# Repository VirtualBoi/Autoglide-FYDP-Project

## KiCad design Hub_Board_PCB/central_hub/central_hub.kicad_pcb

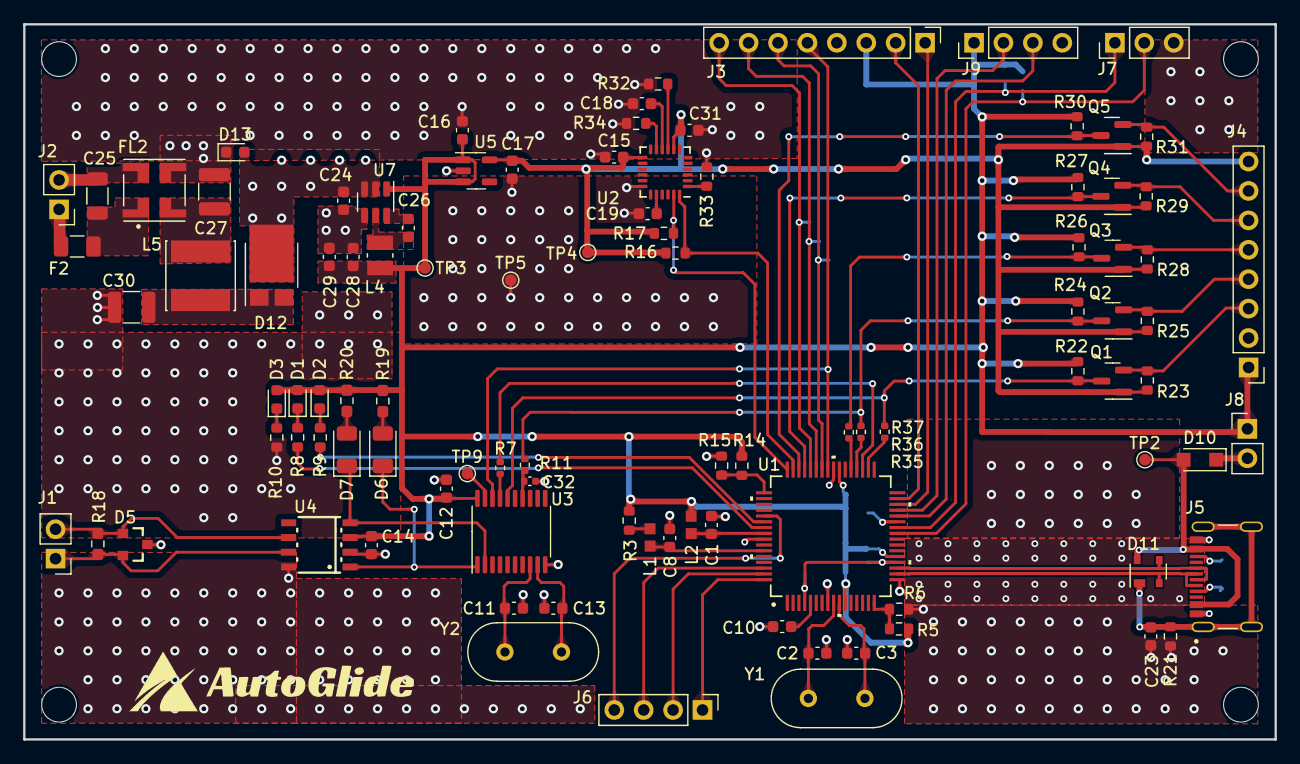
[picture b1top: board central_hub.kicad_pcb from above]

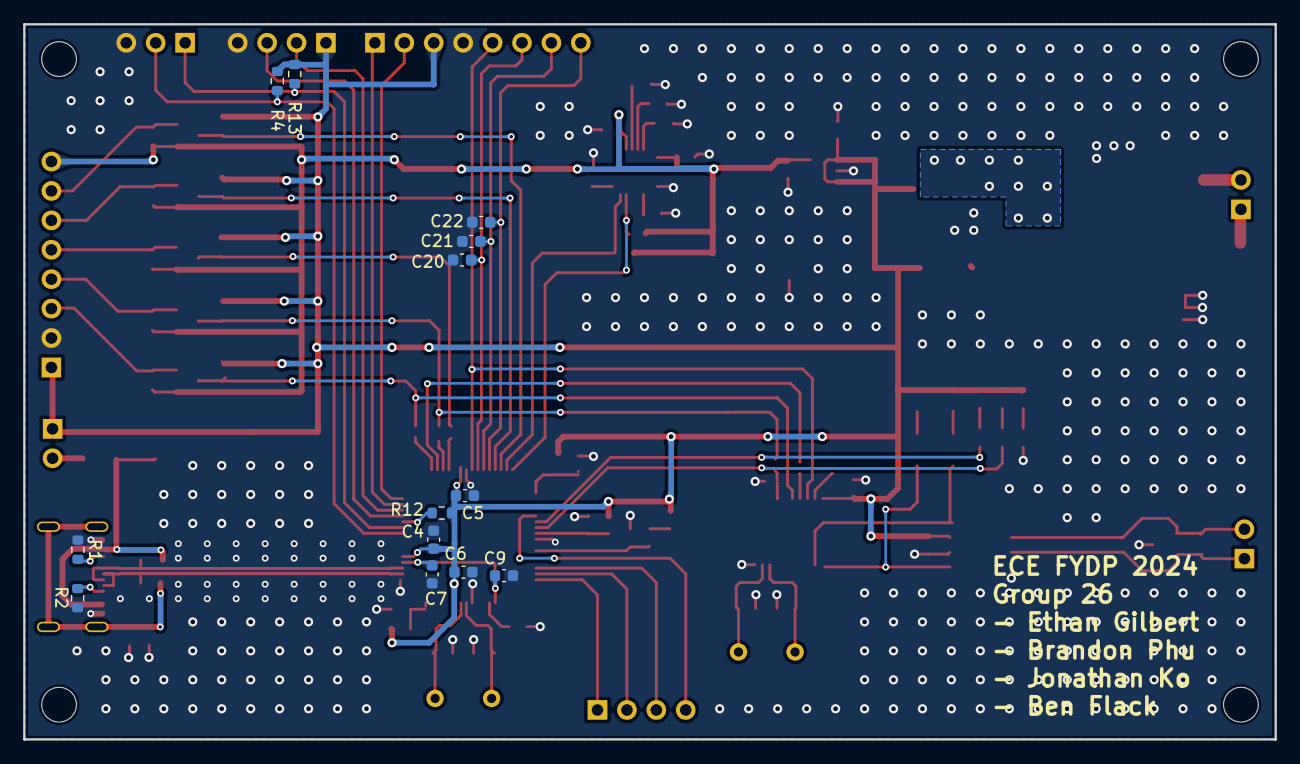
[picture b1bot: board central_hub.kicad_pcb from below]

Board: 2 copper layers, 108.0 x 61.7 mm, 116 parts (13 on the bottom side), 79 nets.

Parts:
C1, C5, C6, C9: 100nF; C_0603_1608Metric
C2, C3, C11, C13: 22p; C_0603_1608Metric
C4, C7, C10: 4.7uF; C_0603_1608Metric
C8: 1uF; C_0603_1608Metric
C12, C14, C15: 0.1u; C_0603_1608Metric
C16, C17: 1u; C_0603_1608Metric
C18: 0.1uF; C_0603_1608Metric
C19: 2.2n; C_0603_1608Metric
C20, C21, C22: 10nF; C_0603_1608Metric
C23: 4.7nF; C_0603_1608Metric
C24: 10u; C_0603_1608Metric
C25: 1u; C_1206_3216Metric
C26: 100n; C_0603_1608Metric
C27, C30: 10u; C_1210_3225Metric
C28, C29: 22u; C_0603_1608Metric
C31: 10n; C_0603_1608Metric
C32: 0.1u; C_0402_1005Metric
D1, D2, D3: LED; D_0603_1608Metric
D5: PESD1CAN; SOT23-3
D6, D7: LED; LED_1206_3216Metric
D10: PMEG6020AELRX; Nexperia_CFP3_SOD-123W
D11: PRTR5V0U2X,215; SOT-143
D12: PMEG030V050EPD; Nexperia_CFP15_SOT-1289
D13: 5.0SMDJ16CA; D_0603_1608Metric
F2: 0685T3000-01; Fuse_1206_3216Metric
FL2: DLW5BTM251TQ2L; FIL_DLW5BTZ251TQ2L
H1, H2, H3, H4: MountingHole; MountingHole_3mm
J1: CAN_OUT; PinHeader_1x02_P2.54mm_Vertical
J2, J8: Conn_01x02; PinHeader_1x02_P2.54mm_Vertical
J3, J4: Screw_Terminal_01x08; PinHeader_1x08_P2.54mm_Vertical
J5: CSP-USC16-TR; VALCON_CSP-USC16-TR
J6, J9: Screw_Terminal_01x04; PinHeader_1x04_P2.54mm_Vertical
J7: Conn_01x03; PinHeader_1x03_P2.54mm_Vertical
L1, L2: BLM18PG471SN1D; IND_BLM18_0603_MUR
L4: DFE252012F-4R7M=P2; INDC2520X120N
L5: VLS6045EX-100M; IND_VLS6045EX-100M
Q1, Q2, Q3, Q4, Q5: BSS138; SOT-23
R1, R2, R3, R4, R5, R12, R13: 5.1k; R_0603_1608Metric
R6, R22, R23, R24, R25, R26, R27, R28, R29, R30, R31: 10k; R_0603_1608Metric
R7, R11, R35, R36, R37: 0; R_0402_1005Metric
R8, R9, R10: 330; R_0603_1608Metric
R14: 100k; R_0603_1608Metric
R15: 13.7k; R_0603_1608Metric
R16, R17, R32, R33, R34: 4.7k; R_0603_1608Metric
R18: 120; R_0603_1608Metric_Pad0.98x0.95mm_HandSolder
R19, R20: 270; R_0603_1608Metric_Pad0.98x0.95mm_HandSolder
R21: 1M; R_0603_1608Metric
TP2, TP3, TP4, TP5, TP9: TestPoint; TestPoint_Pad_D1.0mm
U1: R7FA4M1AB3CFM; PLQP0064KB-C_REN
U2: MPU-6050; InvenSense_QFN-24_4x4mm_P0.5mm
U3: MCP2515-xST; TSSOP-20_4.4x6.5mm_P0.65mm
U4: TJA1050; SOT96-1
U5: AP2112K-3.3TRG1; SOT-23-5
U7: AP63205WU-7; TSOT-23-6
Y1, Y2: 8M; Crystal_HC49-U_Vertical

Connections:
+3.3V: C15.2, C17.2, C31.1, J4.8, Q1.1 (G), Q2.1 (G), Q3.1 (G), Q4.1 (G), Q5.1 (G), R16.1, R17.1, R23.1, R25.1, R28.1, R29.1, R31.1, TP4.1, U2.8 (VLOGIC), U2.13 (VDD), U5.5 (VOUT)
+5V: C4.2, C5.2, C6.2, C12.1, C14.1, C16.2, C28.2, C29.2, D1.2 (A), D2.2 (A), D3.2 (A), J3.3, J4.1, J8.1, J9.1, L2.2, L4.2, R3.1, R4.1, R5.1, R12.1, R13.1, R14.1, R19.1, R20.1, R22.1, R24.1, R26.1, R27.1, R30.1, TP3.1, U1.11 (VCC), U1.21 (VCC_USB_LDO), U1.39 (VCC), U3.20 (VDD), U4.3 (VCC), U5.1 (VIN), U5.3 (EN), U7.1 (FB)
+12V: C24.2, D12.3 (K), D13.2 (A2), U7.2 (EN), U7.3 (IN)
+BATT: F2.1, J2.1
-BATT: C25.1, FL2.4, J2.2
/CAN/CAN_HI: D5.2, J1.1, R18.2, U4.7 (CANH)
/CAN/CAN_LOW: D5.1, J1.2, R18.1, U4.6 (CANL)
/Connectors/SHIELD2: C23.2, D11.1 (GND), J5.S1 (SHELL_GND), J5.S2 (SHELL_GND), J5.S3 (SHELL_GND), J5.S4 (SHELL_GND), R21.1
/MCU/AREF: L1.2, R3.2
/MCU/MCU_3V3: C7.2, C9.2, U1.4 (VBATT), U1.20 (VCC_USB)
/MCU/P012: R8.2, U1.55 (VREFH/AN007/P012)
/MCU/P013: R9.2, U1.54 (VREFL/AN008/P013)
A0: J6.4, U1.53 (DA0/AN009/P014)
A1: J6.1, U1.64 (AN000/P000)
A2: J6.2, U1.63 (AN001/P001)
A3: J6.3, U1.62 (AN002/P002)
BOOT: J7.1, R13.2, U1.26 (MD/P201)
CC1: J5.A5 (CC1), R2.1
CC2: J5.B5 (CC2), R1.1
D0: J3.2, U1.31 (GTIOC4B/P301)
D1: J3.1, U1.30 (GTIOC4A/P302)
D2: C21.1, J3.7, U1.43 (GTIOC1A/P105)
D3: C22.1, J3.8, U1.44 (GTIOC1B/P104)
D4: Q4.3 (D), R27.2, U1.45 (GTIOC2A/AN019/P103)
D4_3.3V: J4.6, Q4.2 (S), R29.2
D5: Q5.3 (D), R30.2, U1.46 (ADTRG0/GTIOC2B/AN020/P102)
D5_3.3V: J4.7, Q5.2 (S), R31.2
D6: C20.1, J3.6, U1.42 (GTIOC0B/P106)
D7: J3.5, U1.41 (GTIOC0A/P107), U3.18 (~CS)
D8: J9.3, U1.28 (GTIOC7A/P304)
D9: J9.2, U1.29 (GTIOC7B/P303)
D10: Q3.3 (D), R26.2, R37.1
D10_3.3V: J4.5, Q3.2 (S), R28.2
D11: Q1.3 (D), R22.2, R35.1, U3.16 (SI)
D11_3.3V: J4.3, Q1.2 (S), R23.2
D12: R7.2, U1.35 (CRX0/TDI/GTIOC1B/P110)
D13: Q2.3 (D), R11.2, R24.2, R36.1
D13_3.3V: J4.4, Q2.2 (S), R25.2
GND: C1.1, C2.1, C3.1, C4.1, C5.1, C6.1, C7.1, C8.1, C9.1, C10.1, C11.1, C12.2, C13.1, C14.2, C15.1, C16.1, C17.1, C18.1, C19.1, C20.2, C21.2, C22.2, C23.1, C24.1, C27.1, C28.1, C29.1, C30.1, C31.2, C32.2, D5.3, D13.1 (A1), FL2.3, J3.4, J4.2, J5.A1 (GND_A), J5.A12 (GND_A), J5.B1 (GND_B), J5.B12 (GND_B), J7.3, J9.4, R1.2, R2.2, R6.2, R10.2, R15.2, R21.2, R32.2, R33.2, R34.2, TP5.1, U1.8 (VSS), U1.17 (VSS_USB), U1.40 (VSS), U1.57 (AVSS0), U2.18 (GND), U3.10 (VSS), U4.2 (GND), U4.8 (S), U5.2 (GND), U7.4 (GND)
unnamed: C25.2, F2.2, FL2.1
unnamed: C27.2, FL2.2, L5.1
unnamed: C30.2, D12.1 (A), D12.2 (A), L5.2
unnamed: D1.1 (K), R8.1
unnamed: D2.1 (K), R9.1
unnamed: D3.1 (K), R10.1
unnamed: D6.2 (A), R19.2
unnamed: D6.1 (K), U3.1 (TXCAN), U4.1 (TXD)
unnamed: D7.2 (A), R20.2
unnamed: D7.1 (K), U3.2 (RXCAN), U4.4 (RXD)
unnamed: C1.2, L2.1, U1.56 (AVCC0)
unnamed: R35.2, U1.34 (CTX0/TDO/SWO/GTIOC1A/P109)
unnamed: R14.2, R15.1, U1.49 (GTIOC2A/AN016/P500)
unnamed: R36.2, U1.36 (GTIOC3A/P111)
unnamed: R37.2, U1.37 (GTIOC3B/P112)
unnamed: R12.2, U1.27 (NMI/INPUT_ONLY_P200)
unnamed: C8.2, L1.1, U1.59 (P010/AN005/VREFH0)
unnamed: C3.2, U1.10 (P212/GTIOC0B/EXTAL), Y1.1
unnamed: C2.2, U1.9 (P213/GTIOC0A/XTAL), Y1.2
unnamed: R5.2, R6.1, U1.16 (P407/USB_VBUS/ADTRG0)
unnamed: C10.2, U1.5 (VCL)
unnamed: R32.1, U2.9 (AD0)
unnamed: R33.1, U2.1 (CLKIN)
unnamed: C19.2, U2.20 (CPOUT)
unnamed: R34.1, U2.11 (FSYNC)
unnamed: C18.2, U2.10 (REGOUT)
unnamed: C13.2, U3.9 (OSC1), Y2.1
unnamed: C11.2, U3.8 (OSC2), Y2.2
unnamed: C32.1, R11.1, U3.14 (SCK)
unnamed: R7.1, U3.17 (SO)
unnamed: TP9.1, U3.19 (~RESET)
unnamed: C26.1, U7.6 (BST)
unnamed: C26.2, L4.1, U7.5 (SW)
SCL_Accel: R17.2, U1.48 (GTIOC5B/AN022/P100), U2.23 (SCL)
SDA_Accel: R16.2, U1.47 (GTIOC5A/AN021/P101), U2.24 (SDA)
USB_D+: D11.3 (I/O2), J5.A6 (DP1), J5.B6 (DP2), U1.19 (P914/USB_DP)
USB_D-: D11.2 (I/O1), J5.A7 (DN1), J5.B7 (DN2), U1.18 (P915/USB_DM)
VUSB: D10.2 (A), D11.4 (VCC), J5.A4 (VBUS_A), J5.A9 (VBUS_A), J5.B4 (VBUS_B), J5.B9 (VBUS_B), TP2.1
VUSB_DIODE: D10.1 (K), J8.2
~RESET: J7.2, R4.2, U1.25 (~RES)

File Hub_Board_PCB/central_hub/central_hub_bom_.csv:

Component,Description,Part,References,Value,Footprint,Quantity Per PCB,Datasheet,fp,FP,Voltage,Colour,Check_prices,MF,MP,PROD_ID,Package,SnapEDA_Link,Availability,MANUFACTURER,MAXIMUM_PACKAGE_HEIGHT,PARTREV,Price,Purchase-URL,STANDARD,Tolerance
1,Unpolarized capacitor,C,C2 C3 C11 C13,22p,C_0603_1608Metric,4,~,0603,0603,,,,,,,,,,,,,,,,
2,Unpolarized capacitor,C,C19,2.2n,C_0603_1608Metric,1,~,,0603,,,,,,,,,,,,,,,,
3,Unpolarized capacitor,C,C23,4.7nF,C_0603_1608Metric,1,~,,0603,1kV,,,,,,,,,,,,,,,
4,Unpolarized capacitor,C,C31,10n,C_0603_1608Metric,1,~,,0603,,,,,,,,,,,,,,,,
5,Unpolarized capacitor,C,C1 C5 C6 C9 C12 C14 C15 C18 C26,100nF,C_0603_1608Metric,9,~,0603,0603,,,,,,,,,,,,,,,,
6,Unpolarized capacitor,C,C32,0.1u,C_0402_1005Metric,1,~,,0402,,,,,,,,,,,,,,,,
7,Unpolarized capacitor,C,C8 C16 C17,1uF,C_0603_1608Metric,3,~,,0603,,,,,,,,,,,,,,,,
8,Unpolarized capacitor,C,C25,1u,C_1206_3216Metric,1,~,,1206,,,,,,,,,,,,,,,,
9,Unpolarized capacitor,C,C4 C7 C10,4.7uF,C_0603_1608Metric,3,~,0603,0603,,,,,,,,,,,,,,,,
10,Unpolarized capacitor,C,C24,10u,C_0603_1608Metric,1,~,,0603,,,,,,,,,,,,,,,,
11,Unpolarized capacitor,C,C27 C30,10u,C_1210_3225Metric,2,~,,1210,,,,,,,,,,,,,,,,
12,Unpolarized capacitor,C,C28 C29,22u,C_0603_1608Metric,2,~,,0603,,,,,,,,,,,,,,,,
13,"400W bidirectional Transient Voltage Suppressor, 18.0Vr, SMA(DO-214AC)",SMAJ18CA,D13,5.0SMDJ16CA,D_0603_1608Metric,1,https://www.littelfuse.com/media?resourcetype=datasheets&ite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,,0603,,,,,,,,,,,,,,,,
14,Light emitting diode,LED,D1 D2 D3,LED,D_0603_1608Metric,3,~,,0603,,GREEN,,,,,,,,,,,,,,
15,Light emitting diode,LED,D6 D7,LED,LED_1206_3216Metric,2,~,,1206,,,,,,,,,,,,,,,,
16,50V Clamp 3A (8/20µs) Ipp Tvs Diode Surface Mount SOT-323,PESD1CAN,D5,PESD1CAN,SOT23-3,1,,,,,,https://www.snapeda.com/parts/PESD1CAN/Nexperia/view-part/?ref=eda,Nexperia USA,PESD1CAN,DIO-12501,SOT-23-3 NXP Semiconductors,https://www.snapeda.com/parts/PESD1CAN/Nexperia/view-part/?ref=snap,,,,,,,,
17,"30V, 5A low Vf MEGA Schottky barrier rectifier, SOT-1289",PMEG030V050EPD,D12,PMEG030V050EPD,Nexperia_CFP15_SOT-1289,1,https://assets.nexperia.com/documents/data-sheet/PMEG030V050EPD.pdf,,,,,,,,,,,,,,,,,,
18,"60V, 2A low leakage current MEGA Schottky barrier rectifier, SOD-123W",PMEG6020AELR,D10,PMEG6020AELRX,Nexperia_CFP3_SOD-123W,1,https://assets.nexperia.com/documents/data-sheet/PMEG6020AELR.pdf,,,,,,,,,,,,,,,,,,
19,"Ultra low capacitance double rail-to-rail ESD protection diode, SOT-143",PRTR5V0U2X,D11,"PRTR5V0U2X,215",SOT-143,1,https://assets.nexperia.com/documents/data-sheet/PRTR5V0U2X.pdf,,,,,,,,,,,,,,,,,,
20,Fuse,Fuse,F2,0685T3000-01,Fuse_1206_3216Metric,1,~,,1206,,,,,,,,,,,,,,,,
21,2 Line Common Mode Choke Surface Mount 250 Ohms @ 100 MHz 5A DCR 20mOhm,DLW5BTM251TQ2L,FL2,DLW5BTM251TQ2L,FIL_DLW5BTZ251TQ2L,1,,,,,,https://www.snapeda.com/parts/DLW5BTM251TQ2L/Murata/view-par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,Murata,DLW5BTM251TQ2L,,Horizontal-6 Murata,https://www.snapeda.com/parts/DLW5BTM251TQ2L/Murata/view-par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,In Stock,Murata Electronics,2.5 mm,N/A,None,https://www.snapeda.com/api/url_track_click_mouser/?unipart_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,Manufacturer recommendations,
22,"Generic screw terminal, single row, 01x02, script generated (kicad-library-utils/schlib/autogen/connector/)",Screw_Terminal_01x02,J1,CAN_OUT,PinHeader_1x02_P2.54mm_Vertical,1,~,,,,,,,,,,,,,,,,,,
23,CSP-USC16-TR Valcon USB Type C Surface Mount PCB Socket,CSP-USC16-TR,J5,CSP-USC16-TR,VALCON_CSP-USC16-TR,1,,,,,,https://www.snapeda.com/parts/CSP-USC16-TR/Valcon/view-part/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,Valcon,CSP-USC16-TR,,None,https://www.snapeda.com/parts/CSP-USC16-TR/Valcon/view-part/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,In Stock,Valcon,3.26 mm,A0,None,https://www.snapeda.com/api/url_track_click_mouser/?unipart_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,Manufacturer Recommendations,
24,"Generic connector, single row, 01x02, script generated (kicad-library-utils/schlib/autogen/connector/)",Conn_01x02,J2 J8,Conn_01x02,PinHeader_1x02_P2.54mm_Vertical,2,~,,,,,,,,,,,,,,,,,,
25,"Generic connector, single row, 01x03, script generated (kicad-library-utils/schlib/autogen/connector/)",Conn_01x03,J7,Conn_01x03,PinHeader_1x03_P2.54mm_Vertical,1,~,,,,,,,,,,,,,,,,,,
26,"Generic screw terminal, single row, 01x04, script generated (kicad-library-utils/schlib/autogen/connector/)",Screw_Terminal_01x04,J6 J9,Screw_Terminal_01x04,PinHeader_1x04_P2.54mm_Vertical,2,~,,,,,,,,,,,,,,,,,,
27,"Generic screw terminal, single row, 01x08, script generated (kicad-library-utils/schlib/autogen/connector/)",Screw_Terminal_01x08,J3 J4,Screw_Terminal_01x08,PinHeader_1x08_P2.54mm_Vertical,2,~,,,,,,,,,,,,,,,,,,
28,,BLM18PG471SN1D,L1 L2,BLM18PG471SN1D,IND_BLM18_0603_MUR,2,BLM18PG471SN1D,,0603,,,,,,,,,,,,,,,,
29,"Inductor with Inductance: 4.7uH Tol. +/-20%, Package: 1008 (2520)",DFE252012F-4R7M=P2,L4,DFE252012F-4R7M=P2,INDC2520X120N,1,,,,,,https://www.snapeda.com/parts/DFE252012F-4R7M=P2/Murata+Elec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,Murata Electronics,DFE252012F-4R7M=P2,,2520 Murata,https://www.snapeda.com/parts/DFE252012F-4R7M=P2/Murata+Elec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,In Stock,,,,None,https://www.snapeda.com/api/url_track_click_mouser/?unipart_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 Electronics&part_name=DFE252012F-4R7M=P2&search_term=dfe252012f-4r7m=p2,,
30,"10 µH Shielded Drum Core, Wirewound Inductor 3.4 A 47mOhm Nonstandard",VLS6045EX-100M,L5,VLS6045EX-100M,IND_VLS6045EX-100M,1,,,,,,https://www.snapeda.com/parts/VLS6045EX-100M/TDK/view-part/?ref=eda,TDK,VLS6045EX-100M,,NON STANDARD-2 TDK,https://www.snapeda.com/parts/VLS6045EX-100M/TDK/view-part/?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,In Stock,TDK,4.5 mm,N/A,None,https://www.snapeda.com/api/url_track_click_mouser/?unipart_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,Manufacturer Recommendations,
31,"50V Vds, 0.22A Id, N-Channel MOSFET, SOT-23",BSS138,Q1 Q2 Q3 Q4 Q5,BSS138,SOT-23,5,https://www.onsemi.com/pub/Collateral/BSS138-D.PDF,,,,,,,,,,,,,,,,,,
32,Resistor,R,R7 R11 R35 R36 R37,0,R_0402_1005Metric,5,~,,0402,,,,,,,,,,,,,,,,
33,Resistor,R,R18,120,R_0603_1608Metric_Pad0.98x0.95mm_HandSolder,1,~,,0603,,,,,,,,,,,,,,,,
34,Resistor,R,R19 R20,270,R_0603_1608Metric_Pad0.98x0.95mm_HandSolder,2,~,,0603,,,,,,,,,,,,,,,,
35,Resistor,R,R8 R9 R10,330,R_0603_1608Metric,3,~,,0603,,,,,,,,,,,,,,,,
36,Resistor,R,R16 R17 R32 R33 R34,4.7k,R_0603_1608Metric,5,~,,0603,,,,,,,,,,,,,,,,
37,Resistor,R,R1 R2 R3 R4 R5 R12 R13,5.1k,R_0603_1608Metric,7,~,0603,0603,,,,,,,,,,,,,,,,
38,Resistor,R,R6 R22 R23 R24 R25 R26 R27 R28 R29 R30 R31,10k,R_0603_1608Metric,11,~,,0603,,,,,,,,,,,,,,,,
39,Resistor,R,R15,13.7k,R_0603_1608Metric,1,~,,0603,,,,,,,,,,,,,,,,0.1%
40,Resistor,R,R14,100k,R_0603_1608Metric,1,~,,0603,,,,,,,,,,,,,,,,0.1%
41,Resistor,R,R21,1M,R_0603_1608Metric,1,~,,0603,,,,,,,,,,,,,,,,
42,"600mA low dropout linear regulator, with enable pin, 3.8V-6V input voltage range, 3.3V fixed positive output, SOT-23-5",AP2112K-3.3,U5,AP2112K-3.3TRG1,SOT-23-5,1,https://www.diodes.com/assets/Datasheets/AP2112.pdf,,,,,,,,,,,,,,,,,,
43,"2A, 1.1MHz Buck DC/DC Converter, fixed 5.0V output voltage, TSOT-23-6",AP63205WU,U7,AP63205WU-7,TSOT-23-6,1,https://www.diodes.com/assets/Datasheets/AP63200-AP63201-AP6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,,,,,,,,,,,,,,,,,,
44,"Stand-Alone CAN Controller with SPI Interface, TSSOP-20",MCP2515-xST,U3,MCP2515-xST,TSSOP-20_4.4x6.5mm_P0.65mm,1,http://ww1.microchip.com/downloads/en/DeviceDoc/21801e.pdf,,,,,,,,,,,,,,,,,,
45,"InvenSense 6-Axis Motion Sensor, Gyroscope, Accelerometer, I2C",MPU-6050,U2,MPU-6050,InvenSense_QFN-24_4x4mm_P0.5mm,1,https://invensense.tdk.com/wp-content/uploads/2015/02/MPU-60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,,,,,,,,,,,,,,,,,,
46,,R7FA4M1AB3CFM,U1,R7FA4M1AB3CFM,PLQP0064KB-C_REN,1,R7FA4M1AB3CFM,,,,,,,,,,,,,,,,,,
47,CAN 1MBd Silent 5V Automotive 8-Pin SO T/R,TJA1050,U4,TJA1050,SOT96-1,1,,,,,,https://www.snapeda.com/parts/TJA1050/NXP+Semiconductors/vie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,NXP Semiconductors,TJA1050,,None,https://www.snapeda.com/parts/TJA1050/NXP+Semiconductors/vie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,Not in stock,,,,None,,,
48,Two pin crystal,Crystal,Y1 Y2,8M,Crystal_HC49-U_Vertical,2,~,,,,,,,,,,,,,,,,,,





Component Groups:,49
Component Count:,107
Fitted Components:,104
Number of PCBs:,1
Total components:,104
Schematic Version:,
Schematic Date:,
PCB Variant:,default
BoM Date:,2023-12-22 5:23:04 PM
Schematic Source:,central_hub.kicad_sch
KiCad Version:,Eeschema 7.0.7

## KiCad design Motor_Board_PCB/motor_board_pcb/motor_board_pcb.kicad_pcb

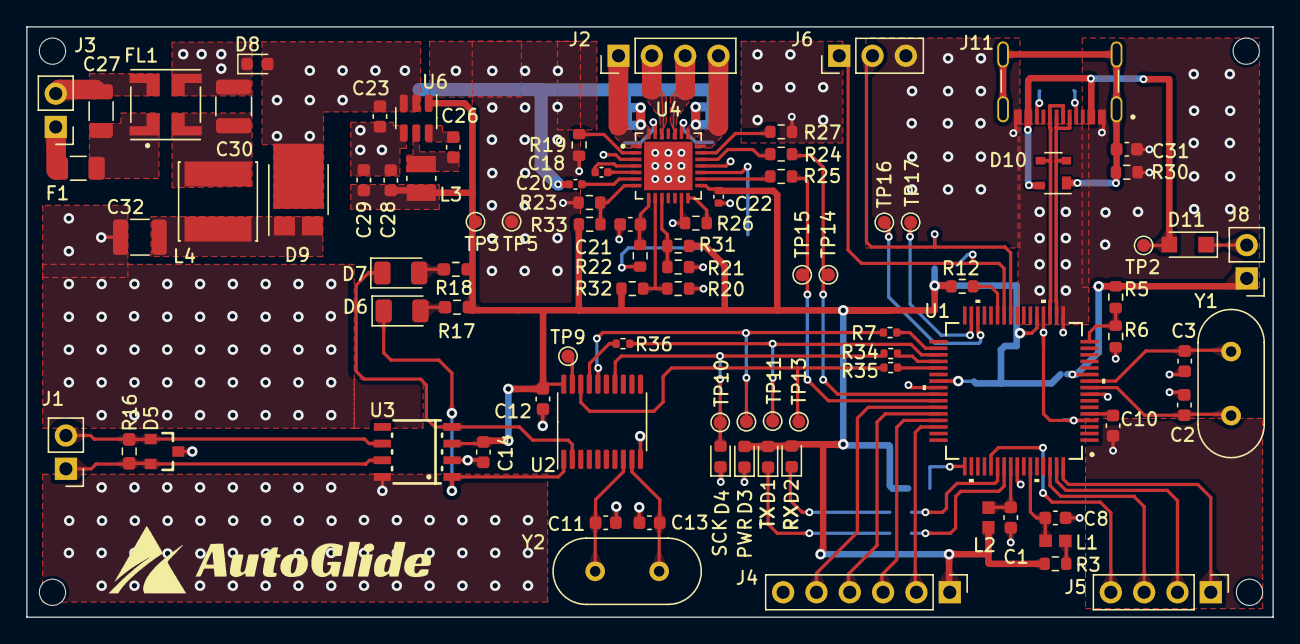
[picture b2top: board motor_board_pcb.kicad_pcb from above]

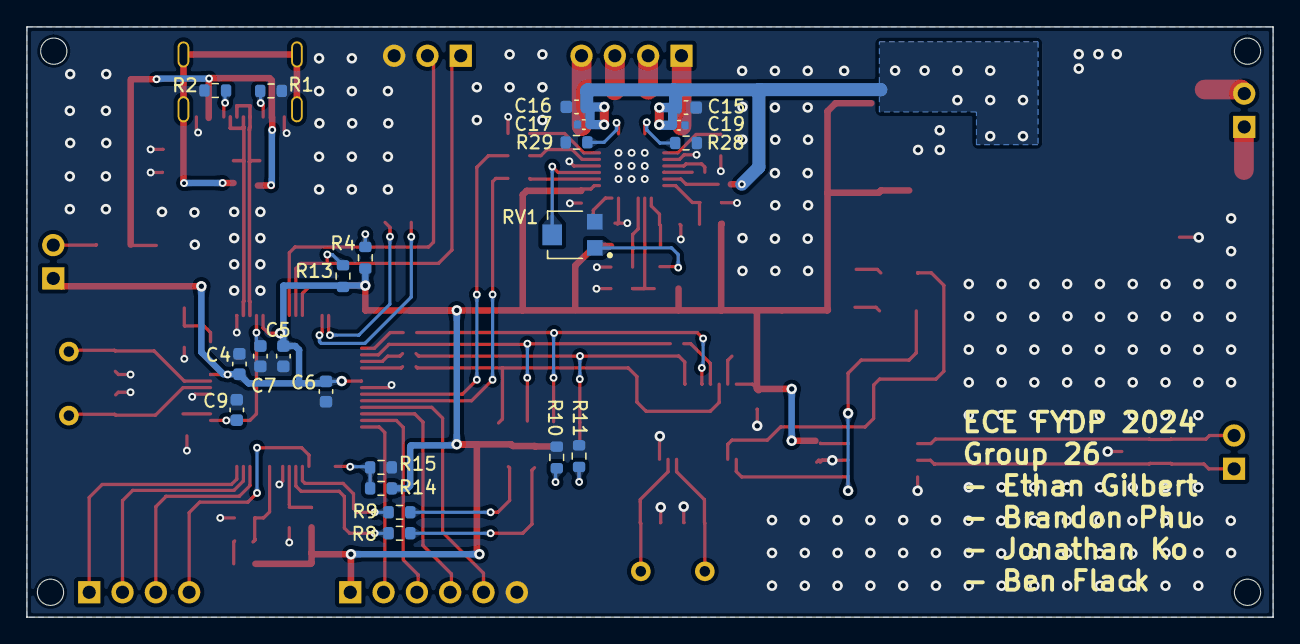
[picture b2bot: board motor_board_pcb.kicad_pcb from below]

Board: 2 copper layers, 95.0 x 45.0 mm, 111 parts (22 on the bottom side), 84 nets.

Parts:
C1, C5, C6, C9: 100nF; C_0603_1608Metric
C2, C3: 15pF; C_0603_1608Metric
C4, C7, C10: 4.7uF; C_0603_1608Metric
C8: 1uF; C_0603_1608Metric
C11, C13: 15p; C_0603_1608Metric
C12, C14: 0.1u; C_0603_1608Metric
C15, C16, C21: 4u7; C_0603_1608Metric
C17, C19, C20, C22: 100n; C_0402_1005Metric
C18: 22n; C_0402_1005Metric
C23: 10u; C_0603_1608Metric
C26: 100n; C_0603_1608Metric
C27: 1u; C_1206_3216Metric
C28, C29: 22u; C_0603_1608Metric
C30, C32: 10u; C_1210_3225Metric
C31: 4.7nF; C_0603_1608Metric
D1, D2, D3, D4: LED; D_0603_1608Metric
D5: PESD1CAN; SOT23-3
D6, D7: LED; LED_1206_3216Metric
D8: 5.0SMDJ16CA; D_0603_1608Metric
D9: PMEG030V050EPD; Nexperia_CFP15_SOT-1289
D10: PRTR5V0U2X,215; SOT-143
D11: PMEG6020AELRX; Nexperia_CFP3_SOD-123W
F1: 0685T3000-01; Fuse_1206_3216Metric
FL1: DLW5BTM251TQ2L; FIL_DLW5BTZ251TQ2L
J1: CAN_OUT; PinHeader_1x02_P2.54mm_Vertical
J2, J5: Screw_Terminal_01x04; PinHeader_1x04_P2.54mm_Vertical
J3, J8: Conn_01x02; PinHeader_1x02_P2.54mm_Vertical
J4: Screw_Terminal_01x06; PinHeader_1x06_P2.54mm_Vertical
J6: Conn_01x03; PinHeader_1x03_P2.54mm_Vertical
J11: CSP-USC16-TR; VALCON_CSP-USC16-TR
L1, L2: BLM18PG471SN1D; IND_BLM18_0603_MUR
L3: DFE252012F-4R7M=P2; INDC2520X120N
L4: VLS6045EX-100M; IND_VLS6045EX-100M
R1, R2, R3, R4, R5, R12, R13: 5.1k; R_0603_1608Metric
R6: 10k; R_0603_1608Metric
R7, R34, R35, R36: 0; R_0402_1005Metric
R8, R9, R10, R11: 330; R_0603_1608Metric
R14: 100k; R_0603_1608Metric
R15: 13.7k; R_0603_1608Metric
R16: 120; R_0603_1608Metric_Pad0.98x0.95mm_HandSolder
R17, R18: 270; R_0603_1608Metric_Pad0.98x0.95mm_HandSolder
R19, R20, R21, R22, R23, R26, R31, R32, R33: 10K; R_0603_1608Metric
R24, R25: 2k; R_0603_1608Metric
R27: 100K; R_0603_1608Metric
R28, R29: 0R11; R_0603_1608Metric
R30: 1M; R_0603_1608Metric
RV1: 10K; TRIM_TC33X-2-103E
TP2, TP3, TP5, TP9, TP10, TP11, TP12, TP13, TP14, TP15, TP16, TP17: TestPoint; TestPoint_Pad_D1.0mm
U1: R7FA4M1AB3CFM; PLQP0064KB-C_REN
U2: MCP2515-xST; TSSOP-20_4.4x6.5mm_P0.65mm
U3: TJA1050; SOT96-1
U4: TMC2209-LA; QFN50P500X500X90-29N
U6: AP63205WU-7; TSOT-23-6
Y1: 16MHz; Crystal_HC49-U_Vertical
Y2: 20M; Crystal_HC49-U_Vertical

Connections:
+5V: C4.2, C5.2, C6.2, C12.1, C14.1, C22.1, C28.2, C29.2, D1.2 (A), D2.2 (A), D3.2 (A), J4.1, J8.1, L2.2, L3.2, R3.1, R4.1, R5.1, R12.1, R13.1, R14.1, R17.1, R18.1, R31.2, R32.2, R33.2, TP3.1, U1.11 (VCC), U1.21 (VCC_USB_LDO), U1.39 (VCC), U2.20 (VDD), U3.3 (VCC), U4.15 (VCC_IO), U6.1 (FB)
+12V: C15.2, C16.2, C17.2, C19.2, C20.2, C23.2, D8.2 (A2), D9.3 (K), U4.22 (VS), U4.28 (VS), U6.2 (EN), U6.3 (IN)
+BATT: F1.1, J3.1
-BATT: C27.1, FL1.4, J3.2
/CAN/CAN_HI: D5.2, J1.1, R16.2, U3.7 (CANH)
/CAN/CAN_LOW: D5.1, J1.2, R16.1, U3.6 (CANL)
/Connectors/SHIELD2: C31.2, D10.1 (GND), J11.S1 (SHELL_GND), J11.S2 (SHELL_GND), J11.S3 (SHELL_GND), J11.S4 (SHELL_GND), R30.1
/MCU/AREF: L1.2, R3.2
/MCU/MCU_3V3: C7.2, C9.2, U1.4 (VBATT), U1.20 (VCC_USB)
/MCU/P012: R8.2, U1.55 (VREFH/AN007/P012)
/MCU/P013: R9.2, U1.54 (VREFL/AN008/P013)
/Motor_Driver/5VOUT: C21.2, R22.2, U4.8 (5VOUT)
/Motor_Driver/OUTA1: J2.3, U4.24 (OUTA1)
/Motor_Driver/OUTA2: J2.4, U4.21 (OUTA2)
/Motor_Driver/OUTB1: J2.2, U4.26 (OUTB1)
/Motor_Driver/OUTB2: J2.1, U4.1 (OUTB2)
A0: J5.4, U1.53 (DA0/AN009/P014)
A1: J5.1, U1.64 (AN000/P000)
A2: J5.2, U1.63 (AN001/P001)
A3: J5.3, U1.62 (AN002/P002)
BOOT: J6.1, R13.2, U1.26 (MD/P201)
CC1: J11.A5 (CC1), R2.1
CC2: J11.B5 (CC2), R1.1
D0: TP17.1, U1.31 (GTIOC4B/P301)
D1: TP16.1, U1.30 (GTIOC4A/P302)
D2: J4.5, U1.43 (GTIOC1A/P105)
D3: J4.4, U1.44 (GTIOC1B/P104)
D4: J4.3, U1.45 (GTIOC2A/AN019/P103)
D5: J4.2, U1.46 (ADTRG0/GTIOC2B/AN020/P102)
D6: R25.2, TP15.1, U1.42 (GTIOC0B/P106)
D7: R24.2, TP14.1, U1.41 (GTIOC0A/P107)
D10: R35.1, TP13.1, U2.18 (~CS)
D11: R7.1, TP12.1, U2.16 (SI)
D12: R36.1, TP11.1, U1.35 (CRX0/TDI/GTIOC1B/P110)
D13: D4.2 (A), R34.1, TP10.1, U2.14 (SCK)
GND: C1.1, C2.1, C3.1, C4.1, C5.1, C6.1, C7.1, C8.1, C9.1, C10.1, C11.1, C12.2, C13.1, C14.2, C15.1, C16.1, C17.1, C19.1, C21.1, C22.2, C23.1, C28.1, C29.1, C30.1, C31.1, C32.1, D5.3, D8.1 (A1), FL1.3, J4.6, J6.3, J11.A1 (GND_A), J11.A12 (GND_A), J11.B1 (GND_B), J11.B12 (GND_B), R1.2, R2.2, R6.2, R10.2, R11.2, R15.2, R19.1, R20.1, R21.1, R23.1, R26.1, R27.1, R28.1, R29.1, R30.2, RV1.3, TP5.1, U1.8 (VSS), U1.17 (VSS_USB), U1.40 (VSS), U1.57 (AVSS0), U2.10 (VSS), U3.2 (GND), U3.8 (S), U4.3 (GND), U4.13 (CLK), U4.18 (GND), U4.29 (GND), U6.4 (GND)
unnamed: C27.2, F1.2, FL1.1
unnamed: C30.2, FL1.2, L4.1
unnamed: C32.2, D9.1 (A), D9.2 (A), L4.2
unnamed: D1.1 (K), R8.1
unnamed: D2.1 (K), R9.1
unnamed: D3.1 (K), R10.1
unnamed: D4.1 (K), R11.1
unnamed: D6.2 (A), R17.2
unnamed: D6.1 (K), U2.1 (TXCAN), U3.1 (TXD)
unnamed: D7.2 (A), R18.2
unnamed: D7.1 (K), U2.2 (RXCAN), U3.4 (RXD)
unnamed: R22.1, RV1.1
unnamed: C1.2, L2.1, U1.56 (AVCC0)
unnamed: R7.2, U1.34 (CTX0/TDO/SWO/GTIOC1A/P109)
unnamed: R14.2, R15.1, U1.49 (GTIOC2A/AN016/P500)
unnamed: R34.2, U1.36 (GTIOC3A/P111)
unnamed: R35.2, U1.37 (GTIOC3B/P112)
unnamed: R12.2, U1.27 (NMI/INPUT_ONLY_P200)
unnamed: C8.2, L1.1, U1.59 (P010/AN005/VREFH0)
unnamed: C3.2, U1.10 (P212/GTIOC0B/EXTAL), Y1.1
unnamed: C2.2, U1.9 (P213/GTIOC0A/XTAL), Y1.2
unnamed: R5.2, R6.1, U1.16 (P407/USB_VBUS/ADTRG0)
unnamed: C10.2, U1.5 (VCL)
unnamed: C13.2, U2.9 (OSC1), Y2.1
unnamed: C11.2, U2.8 (OSC2), Y2.2
unnamed: R36.2, U2.17 (SO)
unnamed: TP9.1, U2.19 (~RESET)
unnamed: R19.2, U4.2 (!ENN)
unnamed: R29.2, U4.23 (BRA)
unnamed: R28.2, U4.27 (BRB)
unnamed: C18.1, U4.5 (CPI)
unnamed: C18.2, U4.4 (CPO)
unnamed: R24.1, U4.19 (DIR)
unnamed: R20.2, R32.1, U4.9 (MS1_AD0)
unnamed: R21.2, R31.1, U4.10 (MS2_AD1)
unnamed: R26.2, U4.14 (PDN_UART)
unnamed: R23.2, R33.1, U4.7 (SPREAD)
unnamed: R27.2, U4.20 (STDBY)
unnamed: R25.1, U4.16 (STEP)
unnamed: C20.1, U4.6 (VCP)
unnamed: RV1.2, U4.17 (VREF)
unnamed: C26.1, U6.6 (BST)
unnamed: C26.2, L3.1, U6.5 (SW)
USB_D+: D10.3 (I/O2), J11.A6 (DP1), J11.B6 (DP2), U1.19 (P914/USB_DP)
USB_D-: D10.2 (I/O1), J11.A7 (DN1), J11.B7 (DN2), U1.18 (P915/USB_DM)
VUSB: D10.4 (VCC), D11.2 (A), J11.A4 (VBUS_A), J11.A9 (VBUS_A), J11.B4 (VBUS_B), J11.B9 (VBUS_B), TP2.1
VUSB_DIODE: D11.1 (K), J8.2
~RESET: J6.2, R4.2, U1.25 (~RES)

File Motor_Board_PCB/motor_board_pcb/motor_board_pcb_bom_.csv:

Component,Description,Part,References,Value,Footprint,Quantity Per PCB,Datasheet,FP,Voltage,Colour,Check_prices,MF,MP,PROD_ID,Package,SnapEDA_Link,Availability,MANUFACTURER,MAXIMUM_PACKAGE_HEIGHT,PARTREV,Price,Purchase-URL,STANDARD,Tolerance
1,Unpolarized capacitor,C,C2 C3 C11 C13,22pF,C_0603_1608Metric,4,~,0603,,,,,,,,,,,,,,,,
2,Unpolarized capacitor,C,C31,4.7nF,C_0603_1608Metric,1,~,0603,1kV,,,,,,,,,,,,,,,
3,Unpolarized capacitor,C,C18,22n,C_0402_1005Metric,1,~,0402,,,,,,,,,,,,,,,,
4,Unpolarized capacitor,C,C1 C5 C6 C9 C12 C14 C26,100nF,C_0603_1608Metric,7,~,0603,,,,,,,,,,,,,,,,
5,Unpolarized capacitor,C,C17 C19 C20 C22,100n,C_0402_1005Metric,4,~,0402,,,,,,,,,,,,,,,,
6,Unpolarized capacitor,C,C27,1u,C_1206_3216Metric,1,~,1206,,,,,,,,,,,,,,,,
7,Unpolarized capacitor,C,C8,1uF,C_0603_1608Metric,1,~,0603,,,,,,,,,,,,,,,,
8,Unpolarized capacitor,C,C4 C7 C10 C15 C16 C21,4.7uF,C_0603_1608Metric,6,~,0603,,,,,,,,,,,,,,,,
9,Unpolarized capacitor,C,C23,10u,C_0603_1608Metric,1,~,0603,,,,,,,,,,,,,,,,
10,Unpolarized capacitor,C,C30 C32,10u,C_1210_3225Metric,2,~,1210,,,,,,,,,,,,,,,,
11,Unpolarized capacitor,C,C28 C29,22u,C_0603_1608Metric,2,~,0603,,,,,,,,,,,,,,,,
12,"400W bidirectional Transient Voltage Suppressor, 18.0Vr, SMA(DO-214AC)",SMAJ18CA,D8,5.0SMDJ16CA,D_0603_1608Metric,1,https://www.littelfuse.com/media?resourcetype=datasheets&ite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,,,,,,,,,,,,,,,,,
13,Light emitting diode,LED,D1 D2 D3 D4,LED,D_0603_1608Metric,4,~,0603,,GREEN,,,,,,,,,,,,,,
14,Light emitting diode,LED,D6 D7,LED,LED_1206_3216Metric,2,~,1206,,,,,,,,,,,,,,,,
15,50V Clamp 3A (8/20µs) Ipp Tvs Diode Surface Mount SOT-323,PESD1CAN,D5,PESD1CAN,SOT23-3,1,,,,,https://www.snapeda.com/parts/PESD1CAN/Nexperia/view-part/?ref=eda,Nexperia USA,PESD1CAN,DIO-12501,SOT-23-3 NXP Semiconductors,https://www.snapeda.com/parts/PESD1CAN/Nexperia/view-part/?ref=snap,,,,,,,,
16,"30V, 5A low Vf MEGA Schottky barrier rectifier, SOT-1289",PMEG030V050EPD,D9,PMEG030V050EPD,Nexperia_CFP15_SOT-1289,1,https://assets.nexperia.com/documents/data-sheet/PMEG030V050EPD.pdf,,,,,,,,,,,,,,,,,
17,"60V, 2A low leakage current MEGA Schottky barrier rectifier, SOD-123W",PMEG6020AELR,D11,PMEG6020AELRX,Nexperia_CFP3_SOD-123W,1,https://assets.nexperia.com/documents/data-sheet/PMEG6020AELR.pdf,,,,,,,,,,,,,,,,,
18,"Ultra low capacitance double rail-to-rail ESD protection diode, SOT-143",PRTR5V0U2X,D10,"PRTR5V0U2X,215",SOT-143,1,https://assets.nexperia.com/documents/data-sheet/PRTR5V0U2X.pdf,,,,,,,,,,,,,,,,,
19,Fuse,Fuse,F1,0685T3000-01,Fuse_1206_3216Metric,1,~,1206,,,,,,,,,,,,,,,,
20,2 Line Common Mode Choke Surface Mount 250 Ohms @ 100 MHz 5A DCR 20mOhm,DLW5BTM251TQ2L,FL1,DLW5BTM251TQ2L,FIL_DLW5BTZ251TQ2L,1,,,,,https://www.snapeda.com/parts/DLW5BTM251TQ2L/Murata/view-par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,Murata,DLW5BTM251TQ2L,,Horizontal-6 Murata,https://www.snapeda.com/parts/DLW5BTM251TQ2L/Murata/view-par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,In Stock,Murata Electronics,2.5 mm,N/A,None,https://www.snapeda.com/api/url_track_click_mouser/?unipart_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,Manufacturer recommendations,
21,"Generic screw terminal, single row, 01x02, script generated (kicad-library-utils/schlib/autogen/connector/)",Screw_Terminal_01x02,J1,CAN_OUT,PinHeader_1x02_P2.54mm_Vertical,1,~,,,,,,,,,,,,,,,,,
22,CSP-USC16-TR Valcon USB Type C Surface Mount PCB Socket,CSP-USC16-TR,J11,CSP-USC16-TR,VALCON_CSP-USC16-TR,1,,,,,https://www.snapeda.com/parts/CSP-USC16-TR/Valcon/view-part/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,Valcon,CSP-USC16-TR,,None,https://www.snapeda.com/parts/CSP-USC16-TR/Valcon/view-part/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,In Stock,Valcon,3.26 mm,A0,None,https://www.snapeda.com/api/url_track_click_mouser/?unipart_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,Manufacturer Recommendations,
23,"Generic connector, single row, 01x02, script generated (kicad-library-utils/schlib/autogen/connector/)",Conn_01x02,J3 J8,Conn_01x02,PinHeader_1x02_P2.54mm_Vertical,2,~,,,,,,,,,,,,,,,,,
24,"Generic connector, single row, 01x03, script generated (kicad-library-utils/schlib/autogen/connector/)",Conn_01x03,J6,Conn_01x03,PinHeader_1x03_P2.54mm_Vertical,1,~,,,,,,,,,,,,,,,,,
25,"Generic screw terminal, single row, 01x04, script generated (kicad-library-utils/schlib/autogen/connector/)",Screw_Terminal_01x04,J2 J5,Screw_Terminal_01x04,PinHeader_1x04_P2.54mm_Vertical,2,~,,,,,,,,,,,,,,,,,
26,"Generic screw terminal, single row, 01x06, script generated (kicad-library-utils/schlib/autogen/connector/)",Screw_Terminal_01x06,J4,Screw_Terminal_01x06,PinHeader_1x06_P2.54mm_Vertical,1,~,,,,,,,,,,,,,,,,,
27,,BLM18PG471SN1D,L1 L2,BLM18PG471SN1D,IND_BLM18_0603_MUR,2,BLM18PG471SN1D,0603,,,,,,,,,,,,,,,,
28,"Inductor with Inductance: 4.7uH Tol. +/-20%, Package: 1008 (2520)",DFE252012F-4R7M=P2,L3,DFE252012F-4R7M=P2,INDC2520X120N,1,,,,,https://www.snapeda.com/parts/DFE252012F-4R7M=P2/Murata+Elec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,Murata Electronics,DFE252012F-4R7M=P2,,2520 Murata,https://www.snapeda.com/parts/DFE252012F-4R7M=P2/Murata+Elec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,In Stock,,,,None,https://www.snapeda.com/api/url_track_click_mouser/?unipart_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 Electronics&part_name=DFE252012F-4R7M=P2&search_term=dfe252012f-4r7m=p2,,
29,"10 µH Shielded Drum Core, Wirewound Inductor 3.4 A 47mOhm Nonstandard",VLS6045EX-100M,L4,VLS6045EX-100M,IND_VLS6045EX-100M,1,,,,,https://www.snapeda.com/parts/VLS6045EX-100M/TDK/view-part/?ref=eda,TDK,VLS6045EX-100M,,NON STANDARD-2 TDK,https://www.snapeda.com/parts/VLS6045EX-100M/TDK/view-part/?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,In Stock,TDK,4.5 mm,N/A,None,https://www.snapeda.com/api/url_track_click_mouser/?unipart_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,Manufacturer Recommendations,
30,Resistor,R,R7 R34 R35 R36,0,R_0402_1005Metric,4,~,0402,,,,,,,,,,,,,,,,
31,Resistor,R,R28 R29,0R11,R_0603_1608Metric,2,~,0603,,,,,,,,,,,,,,,,
32,Resistor,R,R16,120,R_0603_1608Metric_Pad0.98x0.95mm_HandSolder,1,~,0603,,,,,,,,,,,,,,,,
33,Resistor,R,R17 R18,270,R_0603_1608Metric_Pad0.98x0.95mm_HandSolder,2,~,0603,,,,,,,,,,,,,,,,
34,Resistor,R,R8 R9 R10 R11,330,R_0603_1608Metric,4,~,0603,,,,,,,,,,,,,,,,
35,Resistor,R,R24 R25,2k,R_0603_1608Metric,2,~,0603,,,,,,,,,,,,,,,,
36,Resistor,R,R1 R2 R3 R4 R5 R12 R13,5.1k,R_0603_1608Metric,7,~,0603,,,,,,,,,,,,,,,,
37,Resistor,R,R6 R19 R20 R21 R22 R23 R26,10k,R_0603_1608Metric,7,~,0603,,,,,,,,,,,,,,,,
38,Resistor,R,R15,13.7k,R_0603_1608Metric,1,~,0603,,,,,,,,,,,,,,,,0.1%
39,Resistor,R,R14 R27,100k,R_0603_1608Metric,2,~,0603,,,,,,,,,,,,,,,,0.1%
40,Resistor,R,R30,1M,R_0603_1608Metric,1,~,0603,,,,,,,,,,,,,,,,
41,Potentiometer,R_Potentiometer,RV1,10K,TRIM_TC33X-2-103E,1,~,,,,,,,,,,,,,,,,,
42,"2A, 1.1MHz Buck DC/DC Converter, fixed 5.0V output voltage, TSOT-23-6",AP63205WU,U6,AP63205WU-7,TSOT-23-6,1,https://www.diodes.com/assets/Datasheets/AP63200-AP63201-AP6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,,,,,,,,,,,,,,,,,
43,"Stand-Alone CAN Controller with SPI Interface, TSSOP-20",MCP2515-xST,U2,MCP2515-xST,TSSOP-20_4.4x6.5mm_P0.65mm,1,http://ww1.microchip.com/downloads/en/DeviceDoc/21801e.pdf,,,,,,,,,,,,,,,,,
44,,R7FA4M1AB3CFM,U1,R7FA4M1AB3CFM,PLQP0064KB-C_REN,1,R7FA4M1AB3CFM,,,,,,,,,,,,,,,,,
45,CAN 1MBd Silent 5V Automotive 8-Pin SO T/R,TJA1050,U3,TJA1050,SOT96-1,1,,,,,https://www.snapeda.com/parts/TJA1050/NXP+Semiconductors/vie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,NXP Semiconductors,TJA1050,,None,https://www.snapeda.com/parts/TJA1050/NXP+Semiconductors/vie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,Not in stock,,,,None,,,
46,,TMC2209-LA,U4,TMC2209-LA,QFN50P500X500X90-29N,1,TMC2209-LA,,,,,,,,,,,,,,,,,
47,Two pin crystal,Crystal,Y2,8M,Crystal_HC49-U_Vertical,1,~,,,,,,,,,,,,,,,,,
48,Two pin crystal,Crystal,Y1,8MHz,Crystal_HC49-U_Vertical,1,~,,,,,,,,,,,,,,,,,





Component Groups:,49
Component Count:,99
Fitted Components:,96
Number of PCBs:,1
Total components:,96
Schematic Version:,
Schematic Date:,
PCB Variant:,default
BoM Date:,2023-12-22 5:25:27 PM
Schematic Source:,motor_board_pcb.kicad_sch
KiCad Version:,Eeschema 7.0.7

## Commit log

2023-09-26 made folder for motor board pcb
2023-09-26 made folder for hub board pcb
2023-09-26 made folder for footprint library
2023-10-03 Added Libraries and schematic for the MCP2515 CAN chip+supporting components (chematic added to the motor board PCB)
2023-10-04 Added footprints for CAN components to motor board PCB
2023-10-04 added balls
2023-10-04 removed balls
2023-10-10 accelerometer footprint
2023-10-24 switching library to MPU6050
2023-10-27 - added central hub schematic
2023-10-30 added MCU sheet to motor driver schematic
2023-10-30 Integrated MCU to Motor board
2023-10-31 added accelerometer
2023-11-01 Added power and motor driver chip schematics
2023-11-01 Nov 1st Meeting. Addressed comments, updated hub board sheets
2023-11-02 - added global net-labels and reorganized pages - 4.0" TFT SPI 480*320 V2.1 display may already have a level-shifter (actually has HR2046, touch screen controller) so may not need to include voltage 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
2023-11-04 - added header for shorting VUSB and +5V
2023-11-06 Added footprints for almost all components
2023-11-09 Added all other footprints... populated all components with NO errors or warnings :)
2023-11-10 Fixed header sizes
2023-11-12 Started Layout (hub board)
2023-11-13 Redid traces... might want auto trace lol
2023-11-14 Added new connectors as per brandons new shifters
2023-11-15 Prelim layout + routing for hub PCB
2023-11-15 Fixed library + power input change
2023-11-15 Library issue fix
2023-11-16 All library changes + hub power changes
2023-11-20 Fixed PCB after last commit
2023-11-22 Initial PCB placement for Motor Board
2023-11-22 Added cap on accel chip and switched power connector
2023-11-23 Meeting Changes
2023-11-23 Meeting additional changes
2023-11-23 - fixed capacitor values on MCU sheet (both central hub and motor board) - added missing Accelerometer componenets - changed BOOT HEADER (both central hub and motor board) - set the Arduino "love" si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
2023-11-24 - added DNP caps for rotary encoder (debouncing)
2023-11-29 Schematic changes before sending to kim
2023-12-05 Motor Board Initial Layout
2023-12-07 Central hub layout first draft (+ some changes to motor driver)
2023-12-08 Small changes to USB connector d+ and d- traces
2023-12-10 Meeting layout updates
2023-12-10 added additional cs pin for display/can
2023-12-10 Jonathan spelling fix
2023-12-10 Testpoint location changes
2023-12-12 Central Hub USB changes
2023-12-12 All usb changes on both boards
2023-12-19 Kim changes + GND pour + TearDrops + Oscillator changes
2023-12-19 minor changes
2023-12-19 Kim changes
2023-12-22 - added footprint labels to schematic symbols
2023-12-22 - added footprint labels to schematic
2023-12-22 Adding bom files for digikey
2023-12-23 Added DigiKey Boms and gerber files
